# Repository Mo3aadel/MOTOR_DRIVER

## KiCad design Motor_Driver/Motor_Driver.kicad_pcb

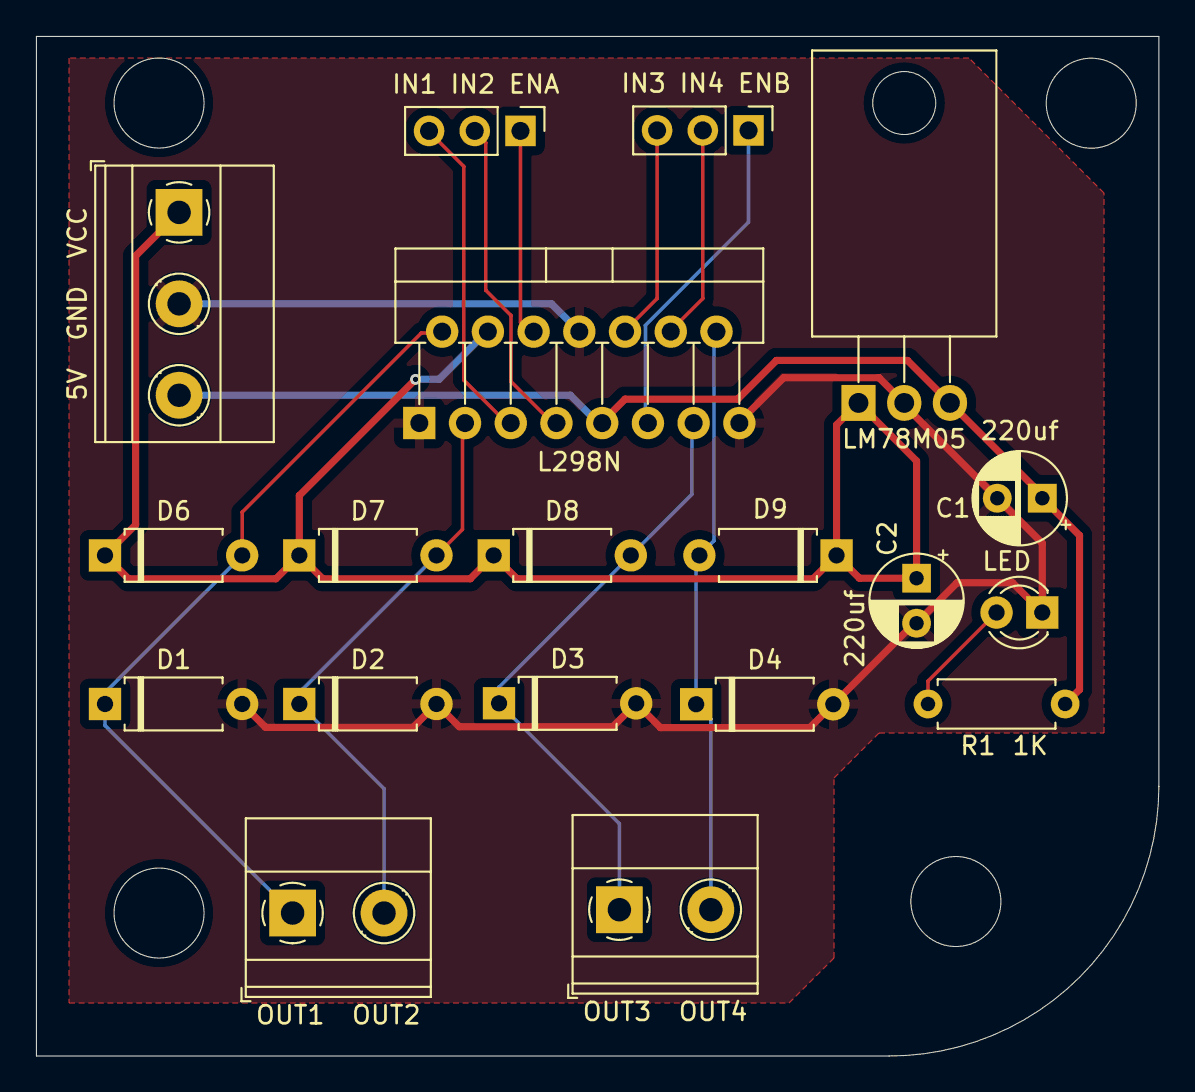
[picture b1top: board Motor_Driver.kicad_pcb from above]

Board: 2 copper layers, 62.4 x 56.6 mm, 19 parts (0 on the bottom side), 14 nets.

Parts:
C1, C2: 220uf; CP_Radial_D5.0mm_P2.50mm
D1, D2, D3, D4, D6, D7, D8, D9: D; D_A-405_P7.62mm_Horizontal
D5: LED; LED_D3.0mm
J1: 5V GND VCC; TerminalBlock_Phoenix_MKDS-1,5-3-5.08_1x03_P5.08mm_Horizont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
J2: IN1 IN2 ENA; PinHeader_1x03_P2.54mm_Vertical
J3: IN3 IN4 ENB; PinHeader_1x03_P2.54mm_Vertical
J4: OUT1 OUT2; TerminalBlock_Phoenix_MKDS-1,5-2-5.08_1x02_P5.08mm_Horizont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
J5: OUT3 OUT4; TerminalBlock_Phoenix_MKDS-1,5-2-5.08_1x02_P5.08mm_Horizont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
R1: 1K; R_Axial_DIN0207_L6.3mm_D2.5mm_P7.62mm_Horizontal
U1: LM78M05; TO-220-3_Horizontal_TabDown
U2: L298N; TO-220-15_P2.54x2.54mm_StaggerOdd_Lead4.58mm_Vertical

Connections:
/5V: C1.1, J1.3, R1.1, U1.3 (VO), U2.9 (Vss)
/A_OUT1: D1.1 (K), D6.2 (A), J4.1, U2.2 (OUT1)
/A_OUT2: D2.1 (K), D7.2 (A), J4.2, U2.3 (OUT2)
/B_OUT3: D3.1 (K), D8.2 (A), J5.1, U2.13 (OUT3)
/B_OUT4: D4.1 (K), D9.2 (A), J5.2, U2.14 (OUT4)
/EnA: J2.1, U2.6 (EnA)
/EnB: J3.1, U2.11 (EnB)
/GND: C1.2, C2.2, D1.2 (A), D2.2 (A), D3.2 (A), D4.2 (A), D5.1 (K), J1.2, U1.2 (GND), U2.1 (SENSE_A), U2.8 (GND), U2.15 (SENSE_B)
/IN1: J2.3, U2.5 (IN1)
/IN2: J2.2, U2.7 (IN2)
/IN3: J3.3, U2.10 (IN3)
/IN4: J3.2, U2.12 (IN4)
/VCC: C2.1, D6.1 (K), D7.1 (K), D8.1 (K), D9.1 (K), J1.1, U1.1 (VI), U2.4 (Vs)
unnamed: D5.2 (A), R1.2
